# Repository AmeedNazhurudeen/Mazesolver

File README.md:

# 🐭 Micromouse Maze Solver Robot

An autonomous micromouse robot designed to solve unknown mazes using real-time mapping, flood fill path planning, and sensor-based closed-loop control.

This project focuses on **embedded robotics, motion control, and intelligent path planning under real-world constraints**.

---

## 🚀 Project Goals

- Explore unknown 16×16 maze environments
- Build an internal map in real-time
- Compute shortest path to the goal cell
- Execute high-speed optimized runs
- Maintain stable motion using PID control

---

## ⚙️ Hardware Overview

- **Microcontroller:** Teensy 2.0 (upgradeable to Teensy 4.0)
- **Motors:** N20 DC motors with encoders
- **Motor Driver:** TB6612FNG / DRV8833 (recommended upgrade)
- **Distance Sensors:** VL53L0X ToF sensors (x3)
- **IMU:** MPU6050 (gyro + accelerometer)
- **Power:** LiPo battery (7.4V recommended)

---

## 🧠 Core System Architecture

The robot is designed as a layered embedded system:

Sensors → Perception → Mapping → Decision → Motion → Control

### Layers:

- **Sensor Layer:** IR / ToF / Encoder / IMU readings
- **Perception Layer:** Wall detection & distance estimation
- **Mapping Layer:** Maze grid construction
- **Decision Layer:** Flood Fill path planning
- **Motion Layer:** Speed profile & turn execution
- **Control Layer:** PID motor control

---

## 🧭 Algorithms Used

### 1. Flood Fill Algorithm (Main Navigation)

Each maze cell is assigned a distance value relative to the goal. The robot always moves toward the lowest-cost neighboring cell.

This ensures:
- Guaranteed shortest path (after full exploration)
- Dynamic adaptation to discovered walls
- Real-time re-planning capability

---

### 2. PID Control System

Used for:
- Wall following stability
- Speed control
- Smooth turning

Inputs:
- Encoder feedback
- IR sensor error

---

### 3. State Machine

The robot operates in two main modes:

- **EXPLORATION MODE**
  - Builds maze map
  - Updates flood fill values dynamically

- **SPEED RUN MODE**
  - Executes optimized shortest path
  - Focuses on maximum speed and stability

---

## 📡 Sensor Strategy

### Primary Sensors:
- IR sensors → real-time wall detection (fast control loop)

### Secondary Sensors:
- VL53L0X ToF → distance estimation & mapping support
- MPU6050 IMU → turning stability and angular correction
- Encoders → precise movement tracking

---

## ⚡ Motion Strategy

- Trapezoidal velocity profile (accelerate → cruise → decelerate)
- Corner smoothing for faster turns
- Straight-line optimization during speed run phase

---

## 🧱 Key Features

- Real-time maze mapping
- Adaptive flood fill path planning
- Sensor fusion-based navigation
- Closed-loop PID motor control
- Exploration + speed run mode switching

---

## 🛠️ Folder Structure

micromouse-maze-solver/
│
├── firmware/ # Embedded robot code
├── hardware/ # PCB, wiring, BOM
├── simulation/ # Maze simulation tools
├── docs/ # Architecture & technical docs
├── tools/ # Calibration & debugging scripts
└── tests/ # Unit tests for algorithms

---

## 📈 Future Improvements

- Upgrade to high-speed microcontroller (Teensy 4.0 / STM32)
- Replace or complement ToF with high-speed IR arrays
- Implement A* hybrid optimization for faster path computation
- Add SLAM-based mapping for advanced research applications
- Improve motion planning using S-curve velocity profiles

---

## 🎯 Applications

- Micromouse robotics competitions
- Autonomous navigation research
- Embedded systems optimization
- Path planning algorithm benchmarking
- Mobile robotics research projects

---

## 🧪 Status

🚧 In Development  
✔ Hardware design ongoing  
✔ Algorithm implementation in progress  
✔ Simulation layer planned  

---

## 📜 License

This project is open-source for educational and research purposes.

---

## 🤖 Author

Built as part of an advanced robotics learning and competition project focused on autonomous navigation systems and embedded intelligence.

---

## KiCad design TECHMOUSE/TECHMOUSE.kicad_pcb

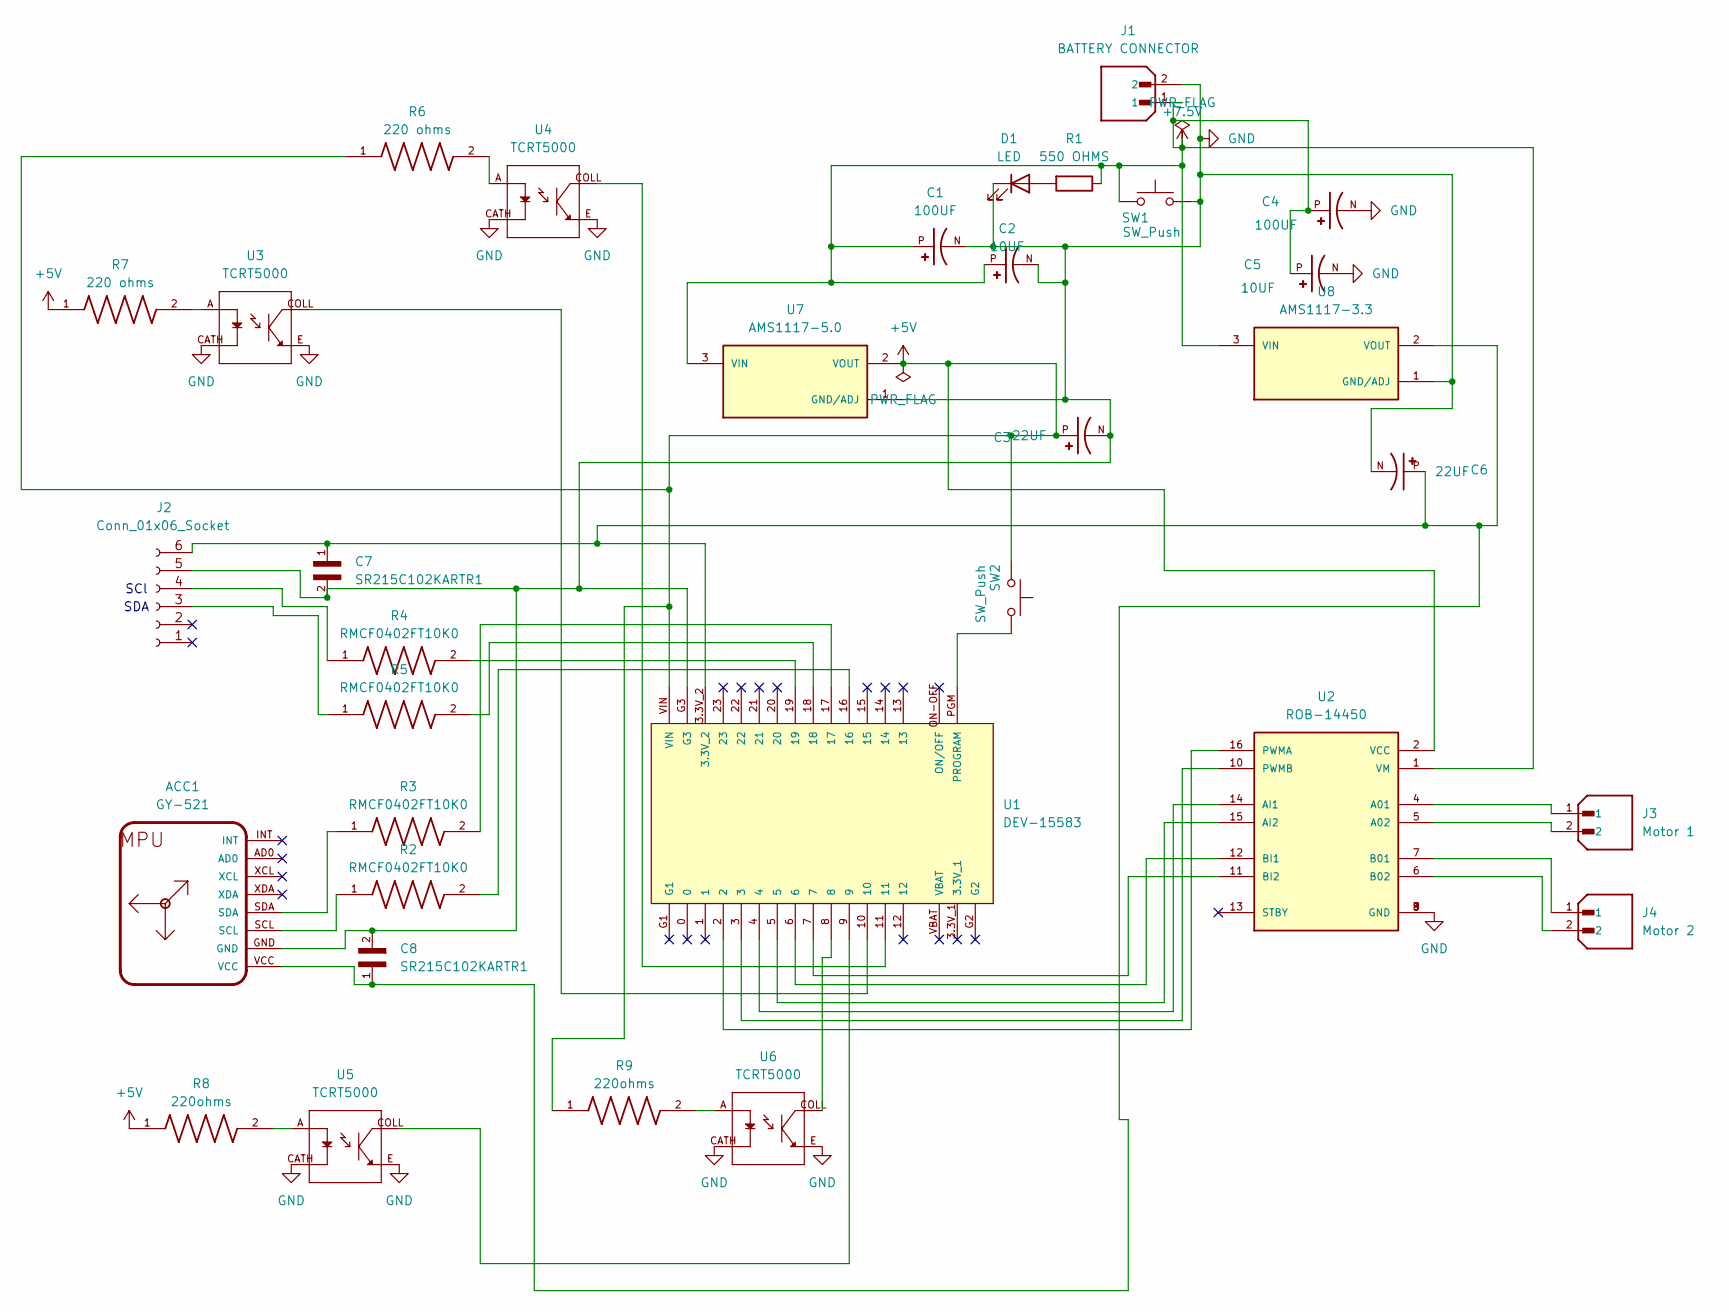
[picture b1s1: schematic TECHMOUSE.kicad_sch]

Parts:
ACC1: GY-521
C1, C4: 100UF; CAPPRD250W50D630H1120; PARTREV 28-FEB-20
C2, C5: 10UF; CAPPRD250W50D630H1120; PARTREV 28-FEB-20
C3, C6: 22UF; CAPPRD250W50D630H1120; PARTREV 28-FEB-20
C7, C8: SR215C102KARTR1; CAPRR508W50L508T317H508; PARTREV 081816
D1: LED; LED_D1.8mm_W1.8mm_H2.4mm_Horizontal_O1.27mm_Z8.2mm
J1: BATTERY CONNECTOR; JST_EH_B2B-EH-A_1x02_P2.50mm_Vertical; PARTREV N/A
J2: Conn_01x06_Socket; PinSocket_1x06_P1.27mm_Vertical
J3: Motor 1; JST_EH_B2B-EH-A_1x02_P2.50mm_Vertical; PARTREV N/A
J4: Motor 2; JST_EH_B2B-EH-A_1x02_P2.50mm_Vertical; PARTREV N/A
R1: 550 OHMS; R_Axial_DIN0204_L3.6mm_D1.6mm_P5.08mm_Horizontal
R2, R3, R4, R5: RMCF0402FT10K0; RESC1005X40
R6, R7: 220 ohms; RESC1005X35N
R8, R9: 220ohms; RESC1005X35N
SW1, SW2: SW_Push; SW_PUSH_6mm
U1: DEV-15583; MODULE_DEV-15583
U2: ROB-14450; MODULE_ROB-14450; PARTREV 11-13-17
U3, U4, U5, U6: TCRT5000; OPTO_TCRT5000; PARTREV 1.7
U7: AMS1117-5.0; SOT229P700X180-4N; PARTREV N/A
U8: AMS1117-3.3; SOT229P700X180-4N; PARTREV N/A

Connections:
+5V: C3.P, R6.1, R7.1, R8.1, R9.1, SW2.1, U1.VIN, U2.2 (VCC), U7.2 (VOUT)
+7.5V: C1.P, C2.P, C4.P, C5.P, J1.1, R1.1, SW1.1, U2.1 (VM), U7.3 (VIN), U8.3 (VIN)
GND: ACC1.GND, C1.N, C2.N, C3.N, C4.N, C5.N, C6.N, C7.2, C8.2, D1.1 (K), J1.2, J2.5, SW1.2, U1.G3, U2.3 (GND), U2.8 (GND), U2.9 (GND), U3.CATH, U3.E, U4.CATH, U4.E, U5.CATH, U5.E, U6.CATH, U6.E, U7.1 (GND/ADJ), U8.1 (GND/ADJ)
unnamed: ACC1.SCL, R2.1
unnamed: ACC1.SDA, R3.1
unnamed: D1.2 (A), R1.2
unnamed: J2.3, R5.1
unnamed: J2.4, R4.1
unnamed: ACC1.VCC, C6.P, C7.1, C8.1, J2.6, U1.3.3V_2, U8.2 (VOUT)
unnamed: R2.2, U1.16
unnamed: R3.2, U1.17
unnamed: R4.2, U1.19
unnamed: R5.2, U1.18
unnamed: R6.2, U4.A
unnamed: R7.2, U3.A
unnamed: R8.2, U5.A
unnamed: R9.2, U6.A
unnamed: SW2.2, U1.PGM (PROGRAM)
unnamed: U1.8, U6.COLL
unnamed: U1.9, U5.COLL
unnamed: U1.10, U3.COLL
unnamed: U1.11, U4.COLL
unnamed: J3.1, U2.4 (A01)
unnamed: J3.2, U2.5 (A02)
unnamed: U1.4, U2.14 (AI1)
unnamed: U1.5, U2.15 (AI2)
unnamed: J4.1, U2.7 (B01)
unnamed: J4.2, U2.6 (B02)
unnamed: U1.6, U2.12 (BI1)
unnamed: U1.7, U2.11 (BI2)
unnamed: U1.2, U2.16 (PWMA)
unnamed: U1.3, U2.10 (PWMB)

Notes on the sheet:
SDA
SCl

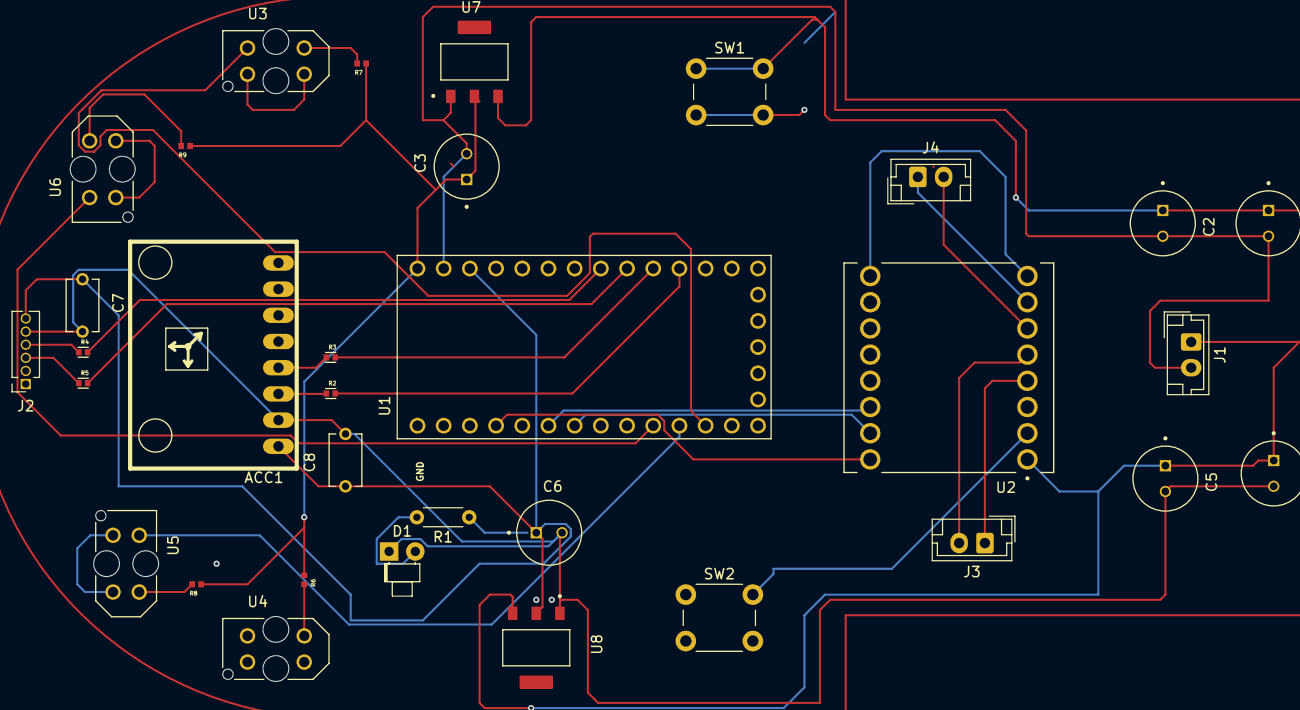
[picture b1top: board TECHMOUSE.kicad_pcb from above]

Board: 2 copper layers, 33 parts (0 on the bottom side), 32 nets.

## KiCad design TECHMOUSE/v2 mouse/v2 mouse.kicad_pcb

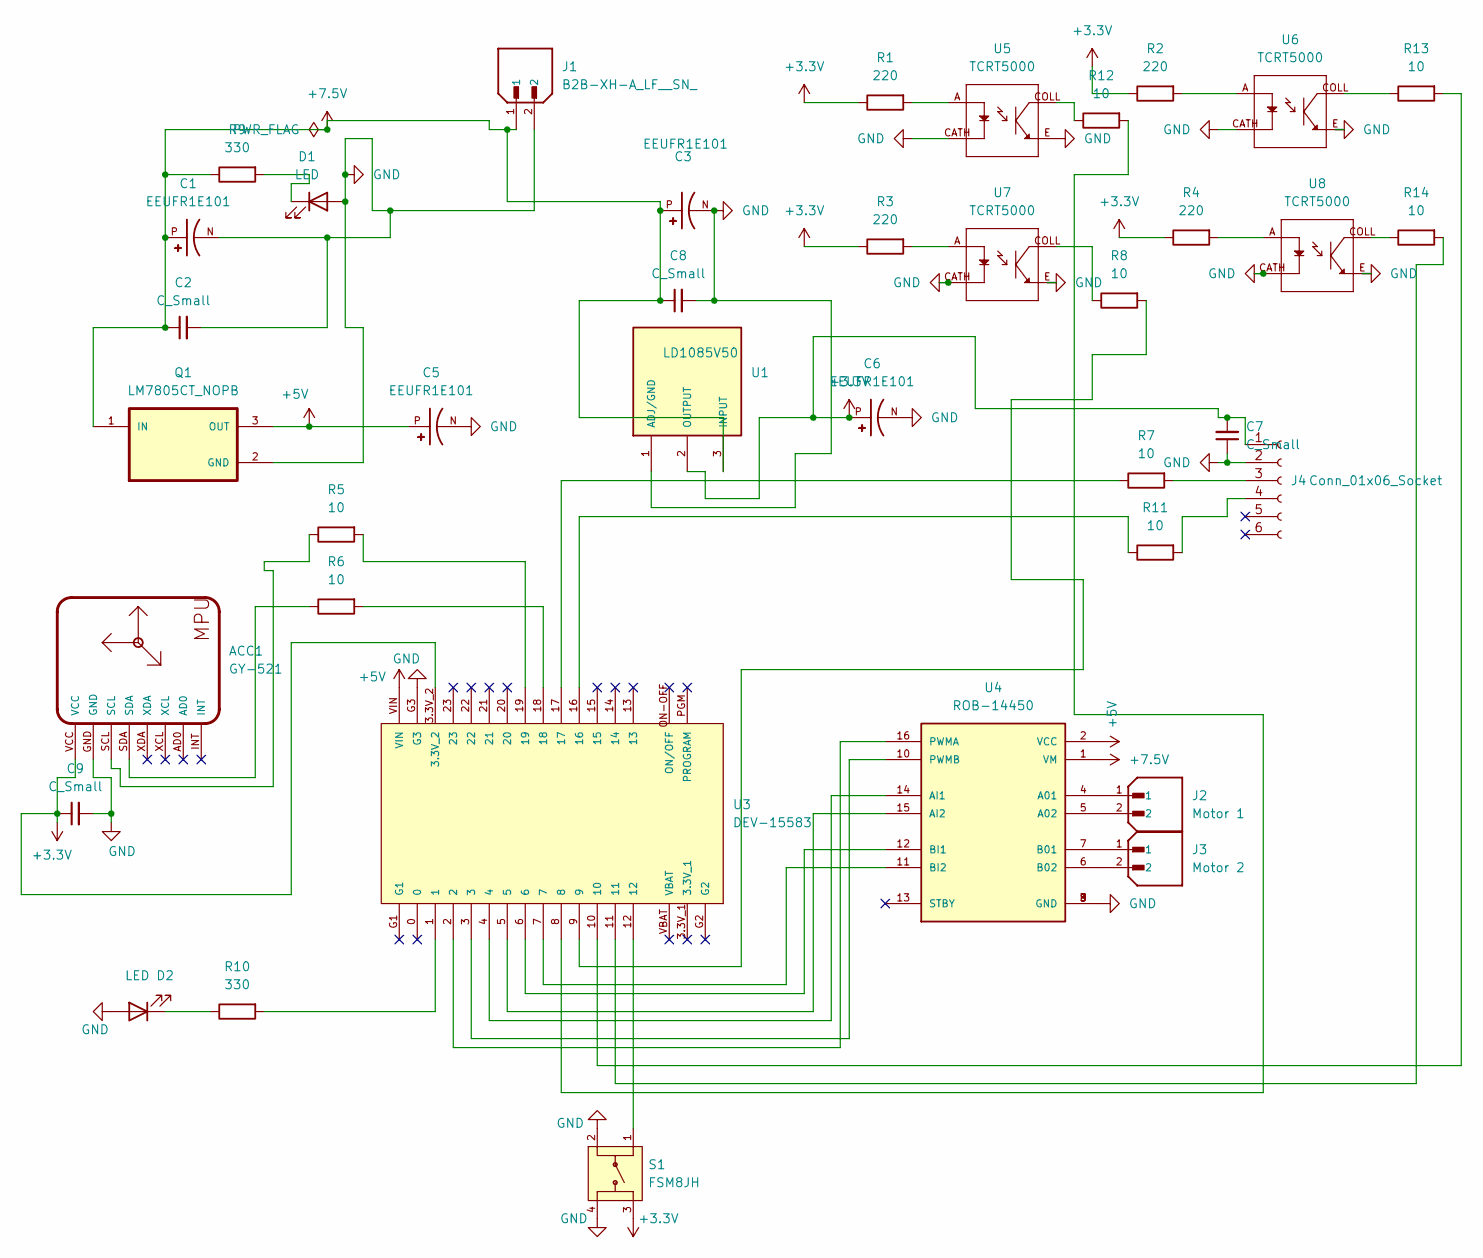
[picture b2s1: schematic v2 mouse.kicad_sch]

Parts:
ACC1: GY-521
C1, C3, C5, C6: EEUFR1E101; CAPPRD250W50D630H1120; PARTREV 28-FEB-20
C2, C7, C8, C9: C_Small; C320C
D1: LED; LED_D3.0mm_Horizontal_O1.27mm_Z6.0mm
D3: LED D2; LED_D3.0mm_Horizontal_O1.27mm_Z6.0mm
J1: B2B-XH-A_LF__SN_; JST_EH_B2B-EH-A_1x02_P2.50mm_Vertical; PARTREV N/A
J2: Motor 1; JST_PH_B2B-PH-K_1x02_P2.00mm_Vertical; PARTREV N/A
J3: Motor 2; JST_PH_B2B-PH-K_1x02_P2.00mm_Vertical; PARTREV N/A
J4: Conn_01x06_Socket; PinSocket_1x06_P1.27mm_Vertical
Q1: LM7805CT_NOPB; TO220; PARTREV LTR
R1, R2, R3, R4: 220; R_Axial_DIN0204_L3.6mm_D1.6mm_P1.90mm_Vertical
R5, R6, R7, R8, R11, R12, R13, R14: 10; R_Axial_DIN0204_L3.6mm_D1.6mm_P1.90mm_Vertical
R9, R10: 330; R_Axial_DIN0204_L3.6mm_D1.6mm_P1.90mm_Vertical
S1: FSM8JH; SW_FSM8JH; PARTREV C10
U1: LD1085V50; TO220
U3: DEV-15583; MODULE_DEV-15583
U4: ROB-14450; MODULE_ROB-14450; PARTREV 11-13-17
U5, U6, U7, U8: TCRT5000; OPTO_TCRT5000; PARTREV 1.7

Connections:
+3.3V: ACC1.VCC, C6.P, C7.2, C9.1, J4.1, R1.1, R2.1, R3.1, R4.1, S1.3, U1.2 (OUTPUT), U3.3.3V_2
+5V: C5.P, Q1.3 (OUT), U3.VIN, U4.2 (VCC)
+7.5V: C1.P, C2.1, C3.P, C8.1, J1.1, Q1.1 (IN), R9.1, U1.3 (INPUT), U4.1 (VM)
GND: ACC1.GND, C1.N, C2.2, C3.N, C5.N, C6.N, C7.1, C8.2, C9.2, D1.2 (A), D3.2 (A), J1.2, J4.2, Q1.2 (GND), S1.2, S1.4, U1.1 (ADJ/GND), U3.G3, U4.3 (GND), U4.8 (GND), U4.9 (GND), U5.CATH, U5.E, U6.CATH, U6.E, U7.CATH, U7.E, U8.CATH, U8.E
unnamed: ACC1.SCL, R5.1
unnamed: ACC1.SDA, R6.1
unnamed: D1.1 (K), R9.2
unnamed: D3.1 (K), R10.1
unnamed: J4.3, R7.2
unnamed: J4.4, R11.2
unnamed: R1.2, U5.A
unnamed: R2.2, U6.A
unnamed: R3.2, U7.A
unnamed: R4.2, U8.A
unnamed: R5.2, U3.19
unnamed: R6.2, U3.18
unnamed: R7.1, U3.17
unnamed: R8.1, U7.COLL
unnamed: R8.2, U3.9
unnamed: R10.2, U3.1
unnamed: R11.1, U3.16
unnamed: R12.1, U5.COLL
unnamed: R12.2, U3.8
unnamed: R13.1, U6.COLL
unnamed: R13.2, U3.10
unnamed: R14.1, U8.COLL
unnamed: R14.2, U3.11
unnamed: S1.1, U3.12
unnamed: J2.1, U4.4 (A01)
unnamed: J2.2, U4.5 (A02)
unnamed: U3.4, U4.14 (AI1)
unnamed: U3.5, U4.15 (AI2)
unnamed: J3.1, U4.7 (B01)
unnamed: J3.2, U4.6 (B02)
unnamed: U3.6, U4.12 (BI1)
unnamed: U3.7, U4.11 (BI2)
unnamed: U3.2, U4.16 (PWMA)
unnamed: U3.3, U4.10 (PWMB)

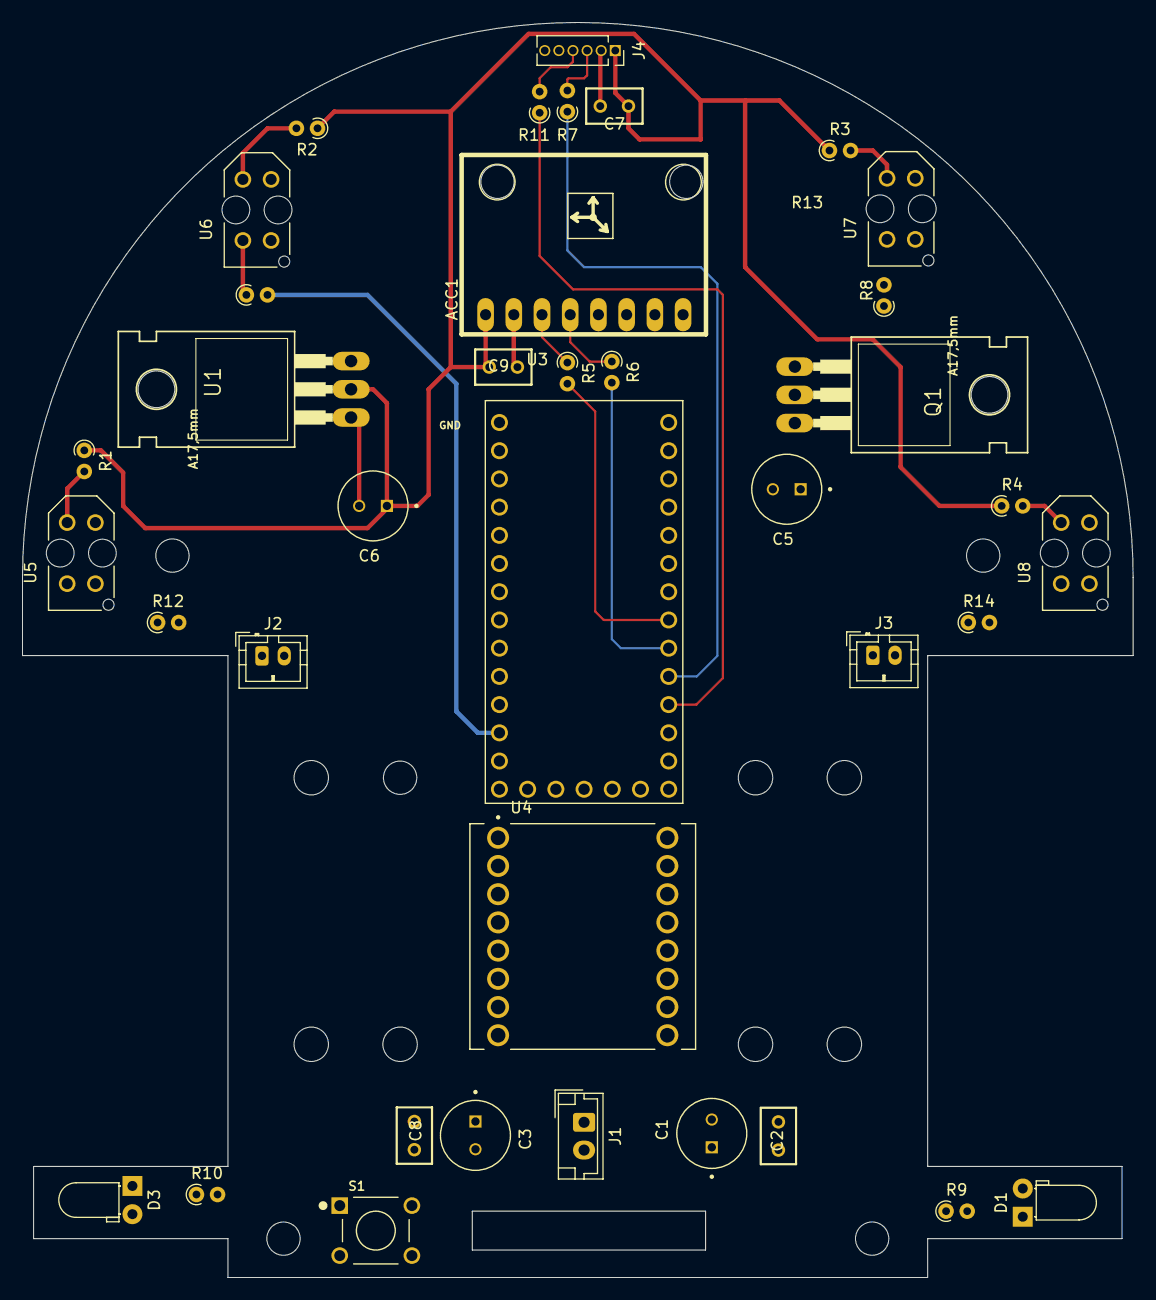
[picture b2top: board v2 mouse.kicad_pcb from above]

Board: 2 copper layers, 100.0 x 113.0 mm, 38 parts (0 on the bottom side), 38 nets.

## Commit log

2026-05-06 Revise README with project overview and details
    Expanded project description and added details about hardware, algorithms, and performance goals.
2026-05-06 Revise README for clarity and completeness
    Updated the README to enhance project overview, goals, and system architecture details.
